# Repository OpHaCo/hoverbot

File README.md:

# HoverBot : the most affordable smooth and silent two wheels drive control

**NOTE: This project is currently abandoned**  
There is more active development over at https://github.com/NiklasFauth/hoverboard-firmware-hack. We already have a working custom firmware for the hoverboard mainboard, complete with ADC, PPM and Nunchuck control. (See the linked video in the description there)

Project has been done in Amiqual4Home Equipex Creativity Lab - https://amiqual4home.inria.fr/

## **Description**

With hoverbot, you can do some vehicle, chassis :
 * supporting up to 264lbs (120kg). 
 * moving silently thanks to two 350W brushless motors in wheels
 * locally or remotely controlled, 
 * at an unbeatable price buying some spare parts :
    * Mother board - 55  eur
    * 36V battery  - 100 eur
    * two wheels   - 160 eur
    * additional components - 40 eur
    * **Total = 355 eur**
 * or more cheaper :
    * just buy an hoverboard and get these parts from it - 260eur
    * additional components - 40eur
    * **Total = 300eur**

Hoverboard are chinese low cost products. Low cost spare parts gives meaningful two wheels drive platform.

You don't have to be an electronic master to do it. To have motors working, you just have to connect hoverbot shield. You can either make this shield by yourself or you can get it from (TODO).

With hoverbot you will be able to drive your : 
* robot
* chair
* old dog
* couch

## **Prerequisities**

### **hardware**

* [Two hoverboard motors] (http://gyro-service.com/moteur/19-moteur.html)
* [Hoverboard mother board] (http://gyro-service.com/cirquit-carte-mere-smart-self-balancing-wheel/17-carte-mere.html)
* [36V battery] (http://gyro-service.com/batteries-samsung-smart-balance-wheel-gyropode/18-battterie-22p-samsumg-ou-de-qualite-equivalente.html)
* [hoverbot shield](#hoverbot-shield) 
* Arduino Teensy 3.1/3.2

## **Setup**

### **Components Analysis**

Refer [ifixit](http://ifixit.org/blog/7821/swagway-teardown-hoverboards/) for a detailed analysis of hoverboard components.
Interesting parts are :
 * how do these components interact?
 * is it possible to control hoverboard externally?

### **Daughterboard / motherboard communication**

Daughterboard can be used either on right/left. So we only bought 1 daughterboard to decode Daughterboard / motherboard exchanged data.
We connected the 2 motherboard / daughterboard connectors to a single motherboard.
In this case when rotating motherboard, wheels are rotating in two different direction.

#### **Protocol**
Probing a logic analyser on daughterboard 4 wire connectors gives some interesting info :
 * logic level = 3.3V
 * bit duration ~ 38.10µs => baud rate ~ 26300kbps
 
 * there is no clock provided on given lines => Async protocol 
 
Is it a standard protocol? 
 * may be UART? Some clues can help... Green and yellow lines of daughterboard are connected to [STM32F103](http://www.st.com/content/ccc/resource/technical/document/reference_manual/59/b9/ba/7f/11/af/43/d5/CD00171190.pdf/files/CD00171190.pdf/jcr:content/translations/en.CD00171190.pdf) PA2 - UART2 TX and PA3 - UART3 RX
In order to get UART parameters : 
 * get maximum frame length taking for example a frame of 0 or a frame of 0/1/0/ and so on... After that you will conclude (helped with Salae logic ananlysers):
**Daughterboard send data to motherboard using 3.3V UART @26300bps - 1 stop bit - no parity bit.** 

#### **Exchanged data**

Here are decoded data with  UART analyzer in Salae Logic software :

Do not move daughterboard, power motherboard and read decoded data. We can see :
 * redondant 256 integer : it is frame start => frame size = 6 9bits integers

Now let's play with photodiode used in daughterboard contacts :
 * if we hide at least one of it  last frame integer = 85
 * otherwise last frame integer = 170
If 170 value is sent to motherboard : motors won't be driven (it means user to not have its feet on hoverboard) (it means user to not have its feet on hoverboard)
 
4 remaining bytes must be decoded : two of these bytes repeats.
Rotating daughterboard gives indication :
 * little move only modify a frame integer => this integer must be low significant 9bit 
 * more rotation modifies other integer    => rotation seems to be encoded on 2 9 bit integers.
Rotating around 0 helps us :
**Angular value is coded in 2x9bits signed integer value (2's complement)**

We can check it is only an angular value applying linear acceleration to daughterboard. In this case angular value do not change.

#### ** Speed sensor **
In wheels some hall sensors are used to get wheel speed (3 sensors per wheel).
On mother board, sensor pulses are filtered using an RC filter. To get speed, we must connect it to hoverbot. 

If we trigger a digital output (channel 0) on a rising edge (channel 0) we do not have a clean signal :

With a zoom :

Small oscillation when V=Vdd/2 generates some falling /rising edges. Because of RC time constant, we can get lot of oscillations leading to some false detections. It could be software filtered (either using timer or checking multiple times read value). As I prefer capturing Hall sensor pulses using external interrupt it is better to have an hardware solution. As Teensy MCU does not have any input schmitt trigger we will add it :

After we have a good pulse detection :

### **hardware** 

In order to control hoverboard we need an external MCU to :
 * send left and right foot angular position => we need two UART Tx lines supporting 9bits UART @ 26300bps
 * optionally read daughterboard current postion (for tests) => we need 1 UART Rx line supporting 9bits UART @ 26300bps
 
Different MCU can be used, we could use UART bitbanging libraries... But a nice solution is to use teensy 3.1/3.2 :
 * it runs @3.3V
 * [9 bit uart supported on Arduino Core] (https://www.pjrc.com/teensy/td_uart.html)
 * 3 avaialble hardware UARTs!

### **software** 

#### Prerequisities
##### Enable 9-Bit UART on Teensy
Edit :

    your_arduino_core_folder/hardware/teensy/avr/cores/teensy3/HardwareSerial.h

Uncomment :

    #define SERIAL_9BIT_SUPPORT

##### Add needed libraries
Several libraries are provided in this repo : 
 * hoverboard : hoverboard control / feddbacks
 * brushless_hall_sensor
 * logger 

If you use arduino IDE, you must create symlinks/shortcuts from these libraries path to Arduino library folder :

    ln -s your_folder/hoverbot/hoverbot_embedded_software/teensy_hoverboard/hoverboard arduino_user_path/libraries/
    ln -s your_folder/hoverbot/hoverbot_embedded_software/teensy_hoverboard/brushless_hall_sensor arduino_user_path/libraries/
    ln -s your_folder/hoverbot/hoverbot_embedded_software/teensy_hoverboard/logger arduino_user_path/libraries/

Then from Arduino IDE add these libraries.

##### Configure logging level
    
Edit 
    your_folder/hoverbot/hoverbot_embedded_software/teensy_hoverboard/logger/logger_config.h
    
and set needed log level (refer your_folder/hoverbot/hoverbot_embedded_software/teensy_hoverboard/logger/README.md)
    
### Arduino sketch

As we saw in our first tests, when same daughterboard is connected to two motherboards/daughterboard connectors :
 * wheels rotating direction is different. Hoverboard is rotating
In this case same angular value on left foot and right foot is sent to motherboard.
In order to have hoverboard moving forward / backward we must apply for example :
 * a positive angular value on right foot daughterboard Uart
 * negative angular value on left foot daughterboard Uart

From that  simple code is provided here :
[Refer code](https://github.com/OpHaCo/hoverbot/blob/master/hoverbot_embedded_software/teensy_hoverboard/teensy_hoverboard.ino)
In `echoGoForward()`  function : it reads current angular value from daughterboard to control hoverboard in forward direction.

After testing we can easily : 
 * control speed of both wheels when it is rotating in different direction (under load or not)

But we cannot :
 * control speed of both wheels when it is rotating is same directions (not under load). **In this case, motors reach needed value but quickly speed up until max speed**
 
 If you want to be able to rotate wheels in the same direction without the motherboard ramping speed to maximum - the phasing of  ***one*** of the motors and corresponding hall sensor can be rotated so that that wheel rotates in the oposite direction for a given input command compared to the other wheel. This means rotating both the power wires and the hall signals. For the standard colour codes a combination that works is (see photo):

- motor power yellow -> motherboard power blue
- motor power blue -> motherboard power yellow
- motor power green -> motherboard power green

- hall motor red -> hall motherboard red
- hall motor yellow -> hall motherboard green
- hall motor blue -> hall motherboard blue
- hall motor green -> hall motherboard yellow
- hall motor black -> hall motherboard black

Whith this phasing rotation on one of the wheels, the ramp to maximum speed will occur if you try and drive both wheels in the opposite direction. 
 
We can suppose, closed loop algorithm on motherboard does not support forward / backward mooving when it is not under load.

## Interfaces
### UART

Hoverboard control over UART can be done running :

    python3 your_folder/hoverbot/hoverbot_gateway_software/examples/hoverboard_uart_control/hoverboard_uart_control.py -p TEENSY_PORT

#### Supported commands :

    power_on

    power_off
    
    set_speed motor1_value motor2_value
    
    x // Manual keyboard control => hoverbot controlled using numeric pad

### SPI
### Wifi
### BLE

## Commands
TODO

### Control commands
TODO
###ROS
## Events
TODO

## Hoverbot shield
### PCB design

## Examples
### Racing chair

## Issues

## References
* http://www.electronicspoint.com/threads/reverse-engineering-a-hoverboard-with-wheels-accelerometer.279098/
* http://drewspewsmuse.blogspot.fr/2016/06/how-i-hacked-self-balancing-scooter.html
* https://developer.mbed.org/users/Thomas_H/code/HoverboardTest/

## Next steps

* improve hoverboard control
* continue cleaning (remove some unused attributes in hoverboard)
* add PID : measure reliable speed from hall sensors
* use all days a reliable racing chair
* make hoverbot shield : deliver CAD
* ROS compatible?
* get error status

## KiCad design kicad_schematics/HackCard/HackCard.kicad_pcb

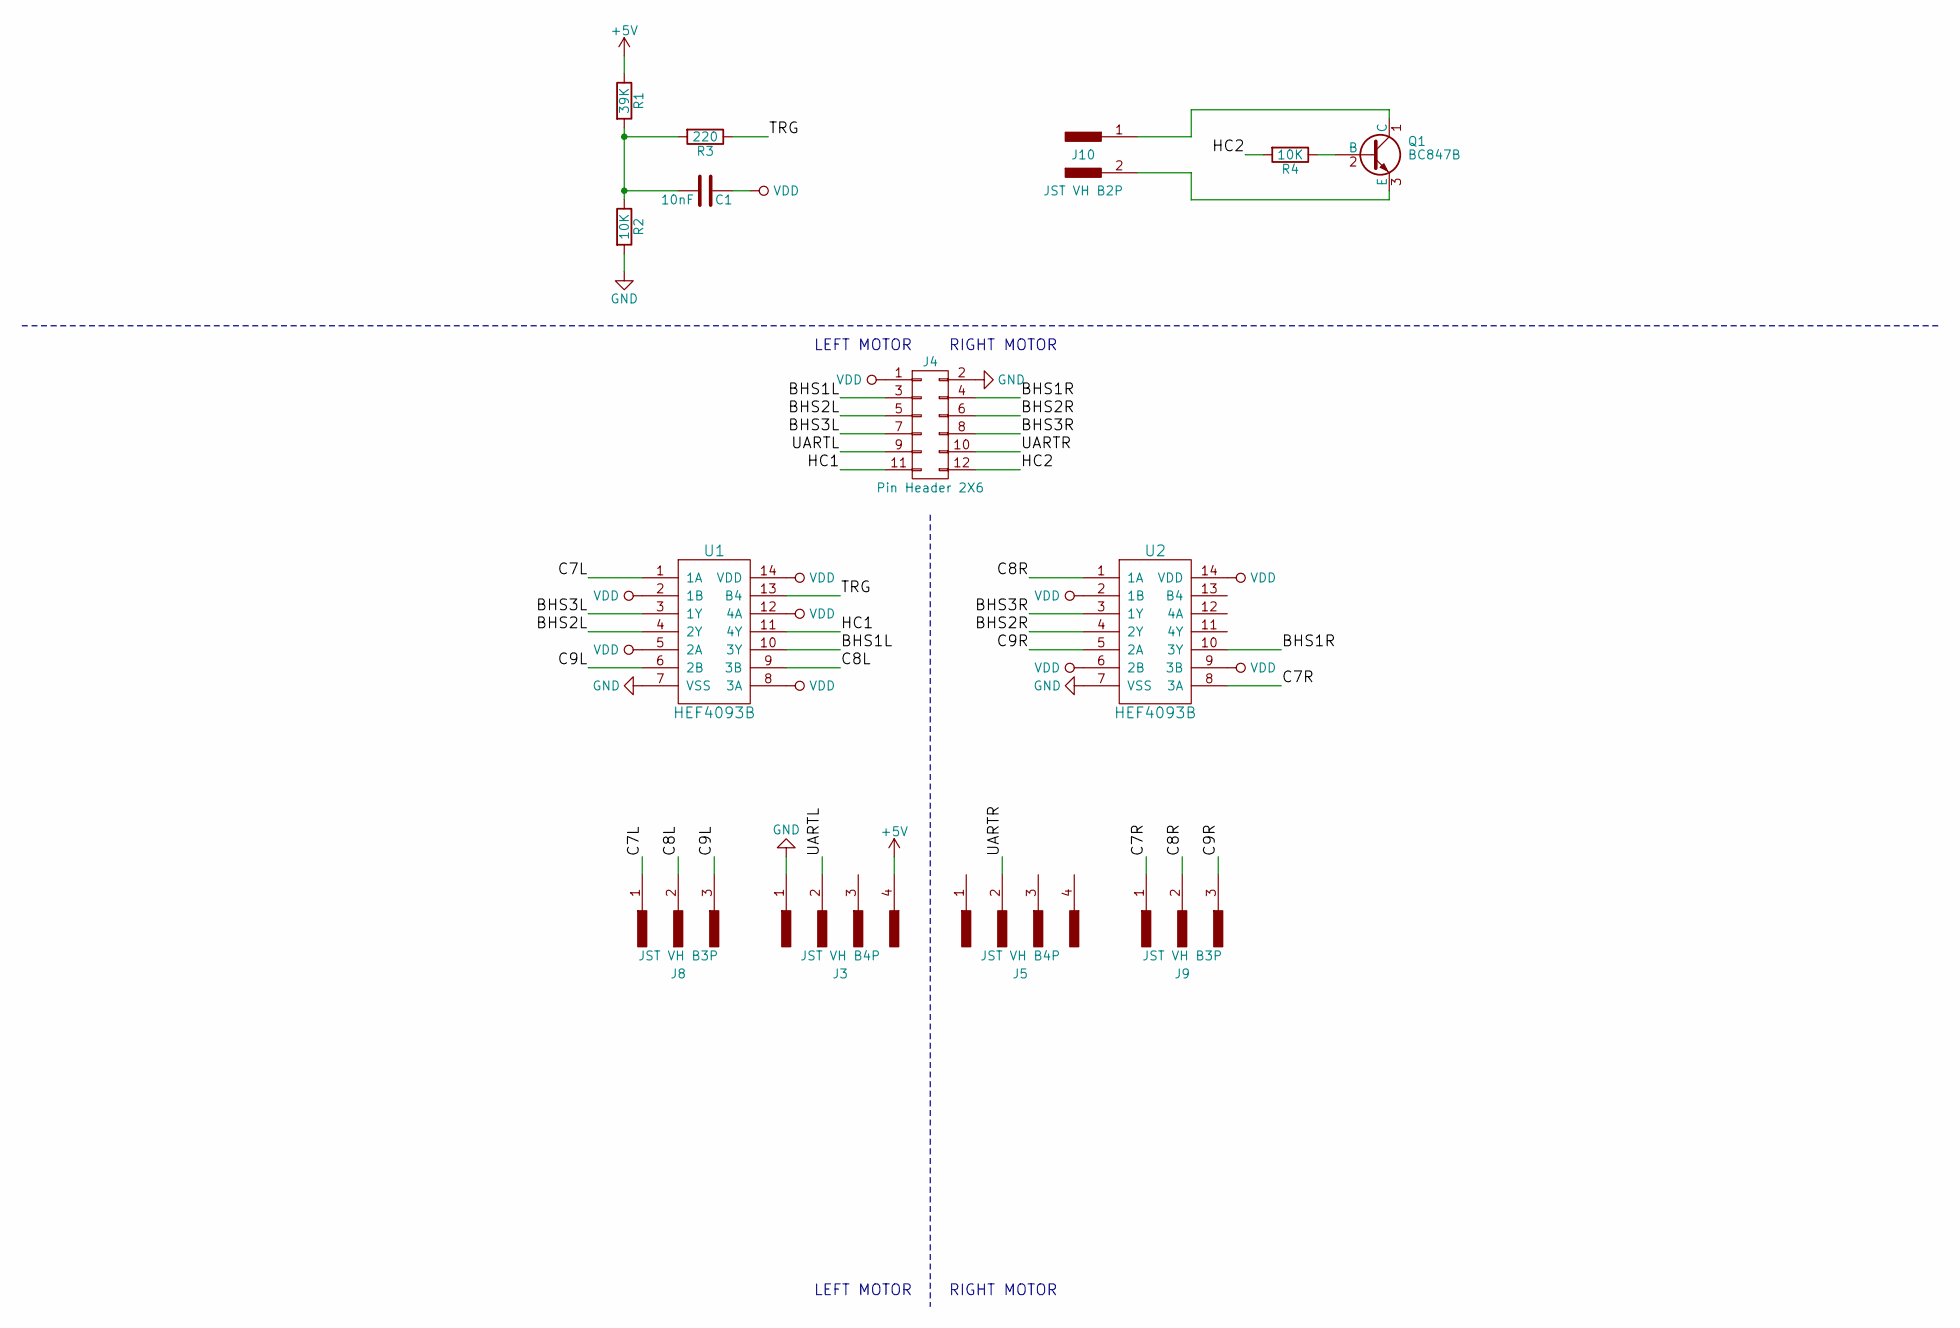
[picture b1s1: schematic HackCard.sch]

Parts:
C1: 10nF; C_0805
J3, J5: JST VH B4P; Pin_Header_Straight_1x04_Pitch2.54mm
J4: Pin Header 2X6; Pin_Header_Straight_2x06_Pitch2.54mm
J8, J9: JST VH B3P; Pin_Header_Straight_1x03_Pitch2.54mm
J10: JST VH B2P; Pin_Header_Straight_1x02_Pitch2.54mm
Q1: BC847B; SOT-23
R1: 39K; R_0805
R2, R4: 10K; R_0805
R3: 220; R_0805
U1, U2: HEF4093B; DIP-14_W7.62mm

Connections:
+5V: J3.4, R1.1
/BHS1L: J4.3, U1.10 (3Y)
/BHS1R: J4.4, U2.10 (3Y)
/BHS2L: J4.5, U1.4 (2Y)
/BHS2R: J4.6, U2.4 (2Y)
/BHS3L: J4.7, U1.3 (1Y)
/BHS3R: J4.8, U2.3 (1Y)
/C7L: J8.1, U1.1 (1A)
/C7R: J9.1, U2.8 (3A)
/C8L: J8.2, U1.9 (3B)
/C8R: J9.2, U2.1 (1A)
/C9L: J8.3, U1.6 (2B)
/C9R: J9.3, U2.5 (2A)
/HC1: J4.11, U1.11 (4Y)
/HC2: J4.12, R4.2
/TRG: R3.1, U1.13 (B4)
/UARTL: J3.2, J4.9
/UARTR: J4.10, J5.2
GND: J3.1, J4.2, R2.2, U1.7 (VSS), U2.7 (VSS)
unnamed: C1.2, R1.2, R2.1, R3.2
unnamed: J10.1, Q1.1 (C)
unnamed: J10.2, Q1.3 (E)
unnamed: Q1.2 (B), R4.1
VDD: C1.1, J4.1, U1.2 (1B), U1.5 (2A), U1.8 (3A), U1.12 (4A), U1.14 (VDD), U2.2 (1B), U2.6 (2B), U2.9 (3B), U2.14 (VDD)

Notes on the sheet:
LEFT MOTOR
RIGHT MOTOR

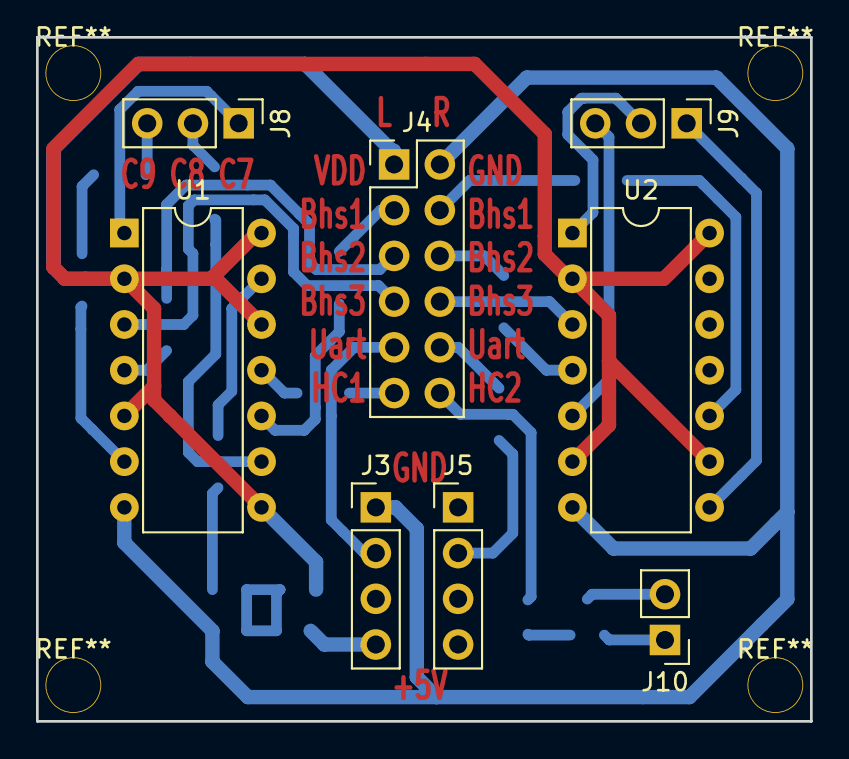
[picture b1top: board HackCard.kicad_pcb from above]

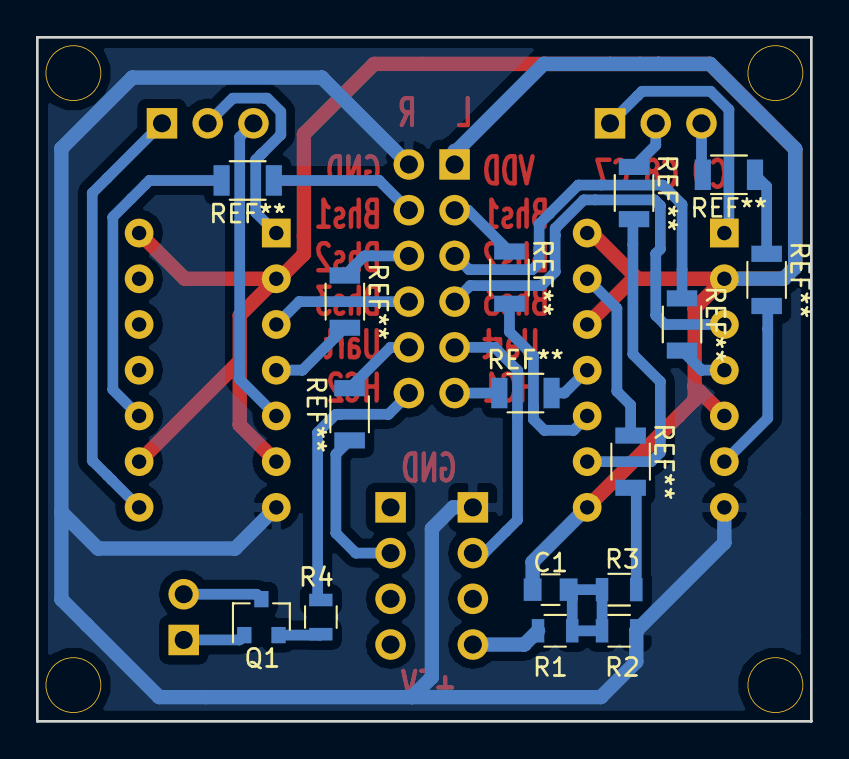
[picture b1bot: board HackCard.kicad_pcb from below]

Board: 2 copper layers, 43.0 x 38.0 mm, 14 parts (6 on the bottom side), 24 nets.

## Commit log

2016-06-09 First tests with teensy3.1
2016-09-02 minor changes
2016-09-04 Minor modif
2016-09-08 Add doc
2016-09-08 bad img URLs
2016-11-18 Update abour forwar direction. TODO adjustments in integral factor
2016-11-25 Add hall decoder
2016-11-29 Preparing a clean Hoverboard object
2016-11-30 Add control methods in Hoverboard class
2016-12-01 First tests on serial
2016-12-06 Add commands to hoverbot terminal
2016-12-07 Add control over numeric keypad
2016-12-07 Workaround to handle sensor IT in objects
2016-12-16 Add imgs
2016-12-16 Add some imgs
2016-12-16 UART speed change
2016-12-16 Modify config
2016-12-16 Clean code. Async processing. Add logger
2016-12-16 update doc
2016-12-16 Squashed 'hoverbot_embedded_software/teensy_hoverboard/logger/' content from commit c66ec33
    git-subtree-dir: hoverbot_embedded_software/teensy_hoverboard/logger
    git-subtree-split: c66ec33e79c361d81ed4afd4e6b1320883942a62
2016-12-16 Add Logger
2016-12-16 Add logger config file
2016-12-16 Update todo
2016-12-19 Add rampUp duration argument to setSpeed. Add timestamp in UART console
2016-12-22 Add hall detection imgs
2016-12-22 debug hall sensor => add schmitt trigger
2016-12-23 Add timestamp in uart terminal
2016-12-23 Autoscroll
2016-12-23 Check power status, add motor1 hall sensors
2017-01-07 Add files via upload
    Motor and hall sensors flipped so that one motor is reversed direction.
2017-01-07 Update README.md
    Update to describe a workaround for the motors ramping to maximum speed
2017-03-22 Squashed 'hoverbot_embedded_software/teensy_hoverboard/pid_controller/' content from commit d9643c1
    git-subtree-dir: hoverbot_embedded_software/teensy_hoverboard/pid_controller
    git-subtree-split: d9643c185318c6f10d6917bc4cfb9b32fbda8fb0
2017-03-23 Minor errors
2017-03-24 Scrolling bug. Split ontent of text widgets into multiple widgets
2017-03-31 Add not blocking call for commander loop
2017-03-31 Add motor monitor
2017-04-04 Add preamble for hoverbot cmds
2017-04-04 Minor modifs
2017-04-05 Add clear, pause, resume for graphs
2017-04-05 get_input does not block anymore
2017-04-05 Add filtered_input
2017-04-05 Minor modifs, add some needed methods
2017-04-05 Add PID, PID debug for both wheels
2017-04-05 log gyro status
2017-04-26 Do not rescale graphs when display paused
2017-04-26 Add command to get current ticks
2017-07-05 add schematic
2017-07-06 text for I/O
2018-05-23 Refer to actively developed repository
    I hope this is okay to you, because your repository is currently the most popular, but contains only information and proof-of-concept, while the one I linked will give you a complete and working hove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
